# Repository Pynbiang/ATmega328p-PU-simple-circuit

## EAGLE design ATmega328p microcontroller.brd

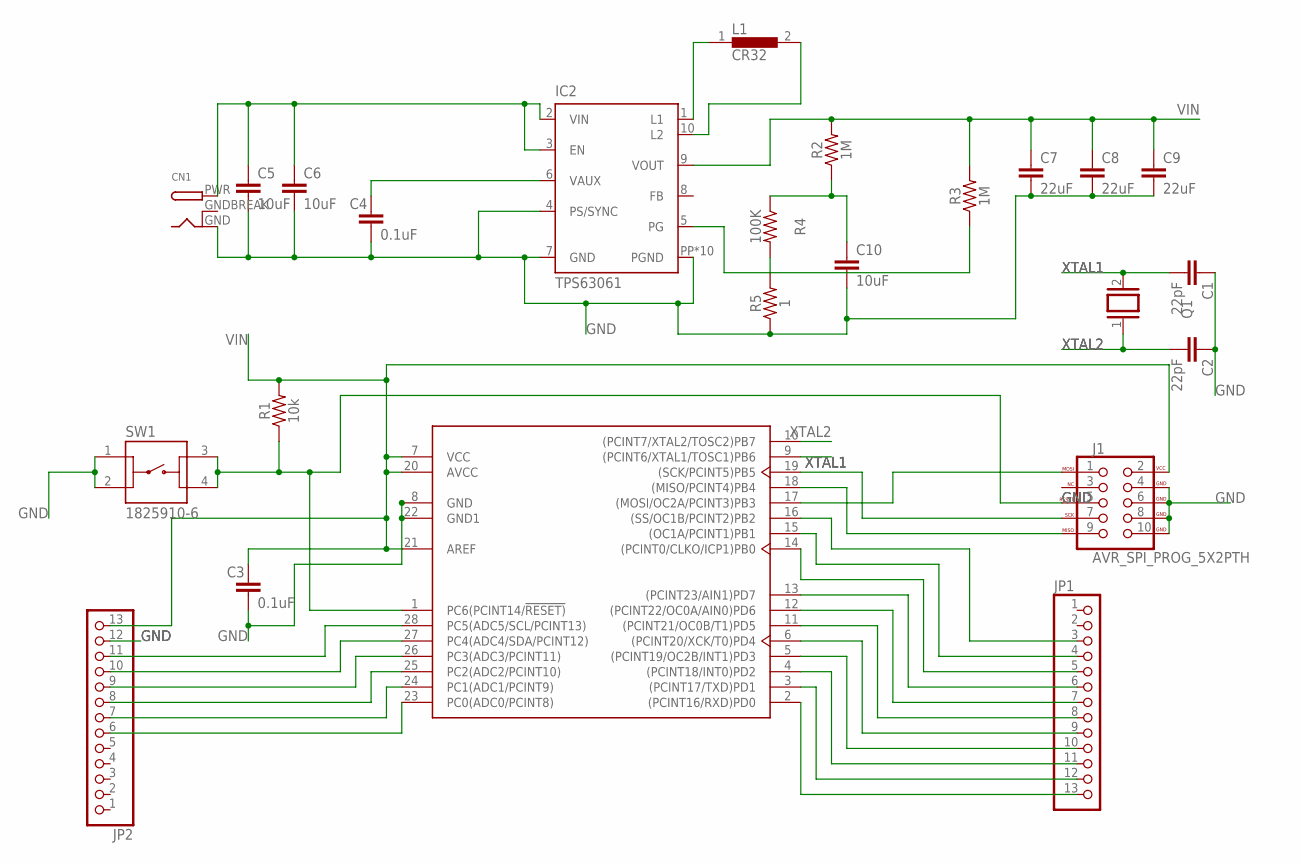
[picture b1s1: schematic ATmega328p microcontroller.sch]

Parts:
C1, C2: 22pF; 0603
C3, C4: 0.1uF; 0402
C5, C6, C10: 10uF; 0603
C7, C8, C9: 22uF; 0805
CN1: DCBARRELPTH; DCJACK_2MM_PTH
IC2: TPS63061; DSC-S-PWSON-N10
J1: AVR_SPI_PROG_5X2PTH; 2X5
JP1, JP2: PINHD-1X13; 1X13
L1: CR32
Q1: XTAL/S; QS
R1: 10k; 0603
R2, R3: 1M; 0603
R4: 100K; 0402
R5: 1; 0603
SW1: 1825910-6
U1: ATMEGA328P-PU; DIP-28

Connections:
GND: C1.1, C2.1, C3.2, C4.2, C5.2, C6.2, C7.2, C8.2, C9.2, C10.2, CN1.GND, IC2.4 (PS/SYNC), IC2.7 (GND), IC2.PP (PGND), IC2.PP@1 (PGND), IC2.PP@2 (PGND), IC2.PP@3 (PGND), IC2.PP@4 (PGND), IC2.PP@5 (PGND), IC2.PP@7 (PGND), IC2.PP@8 (PGND), IC2.PP@9 (PGND), IC2.PP@10 (PGND), J1.4 (GND), J1.6 (GND), J1.8 (GND), J1.10 (GND), JP2.12, R5.1, SW1.1, SW1.2, U1.8 (GND), U1.22 (GND1)
GNDBREAK: CN1.GNDBREAK
unnamed: JP2.11, U1.28 (PC5(ADC5/SCL/PCINT13))
unnamed: J1.7 (SCK), U1.19 ((SCK/PCINT5)PB5)
unnamed: J1.9 (MISO), U1.18 ((MISO/PCINT4)PB4)
unnamed: J1.1 (MOSI), U1.17 ((MOSI/OC2A/PCINT3)PB3)
unnamed: J1.5 (RESET), R1.1, SW1.3, SW1.4, U1.1 (PC6(PCINT14/!RESET))
unnamed: JP1.9, U1.6 ((PCINT20/XCK/T0)PD4)
unnamed: JP1.8, U1.11 ((PCINT21/OC0B/T1)PD5)
unnamed: JP1.7, U1.12 ((PCINT22/OC0A/AIN0)PD6)
unnamed: JP1.13, U1.2 ((PCINT16/RXD)PD0)
unnamed: JP1.12, U1.3 ((PCINT17/TXD)PD1)
unnamed: JP1.11, U1.4 ((PCINT18/INT0)PD2)
unnamed: JP1.10, U1.5 ((PCINT19/OC2B/INT1)PD3)
unnamed: JP1.6, U1.13 ((PCINT23/AIN1)PD7)
unnamed: JP1.5, U1.14 ((PCINT0/CLKO/ICP1)PB0)
unnamed: JP1.4, U1.15 ((OC1A/PCINT1)PB1)
unnamed: JP1.3, U1.16 ((SS/OC1B/PCINT2)PB2)
unnamed: JP2.10, U1.27 (PC4(ADC4/SDA/PCINT12))
unnamed: JP2.9, U1.26 (PC3(ADC3/PCINT11))
unnamed: JP2.8, U1.25 (PC2(ADC2/PCINT10))
unnamed: JP2.7, U1.24 (PC1(ADC1/PCINT9))
unnamed: JP2.6, U1.23 (PC0(ADC0/PCINT8))
unnamed: C5.1, C6.1, CN1.PWR, IC2.2 (VIN), IC2.3 (EN)
unnamed: C4.1, IC2.6 (VAUX)
unnamed: IC2.1 (L1), L1.1
unnamed: IC2.10 (L2), L1.2
unnamed: C10.1, R2.1, R4.1
unnamed: R4.2, R5.2
unnamed: IC2.5 (PG), R3.1
VIN: C3.1, C7.1, C8.1, C9.1, IC2.9 (VOUT), J1.2 (VCC), JP2.13, R1.2, R2.2, R3.2, U1.7 (VCC), U1.20 (AVCC), U1.21 (AREF)
XTAL1: C1.2, Q1.2, U1.9 ((PCINT6/XTAL1/TOSC1)PB6)
XTAL2: C2.2, Q1.1, U1.10 ((PCINT7/XTAL2/TOSC2)PB7)

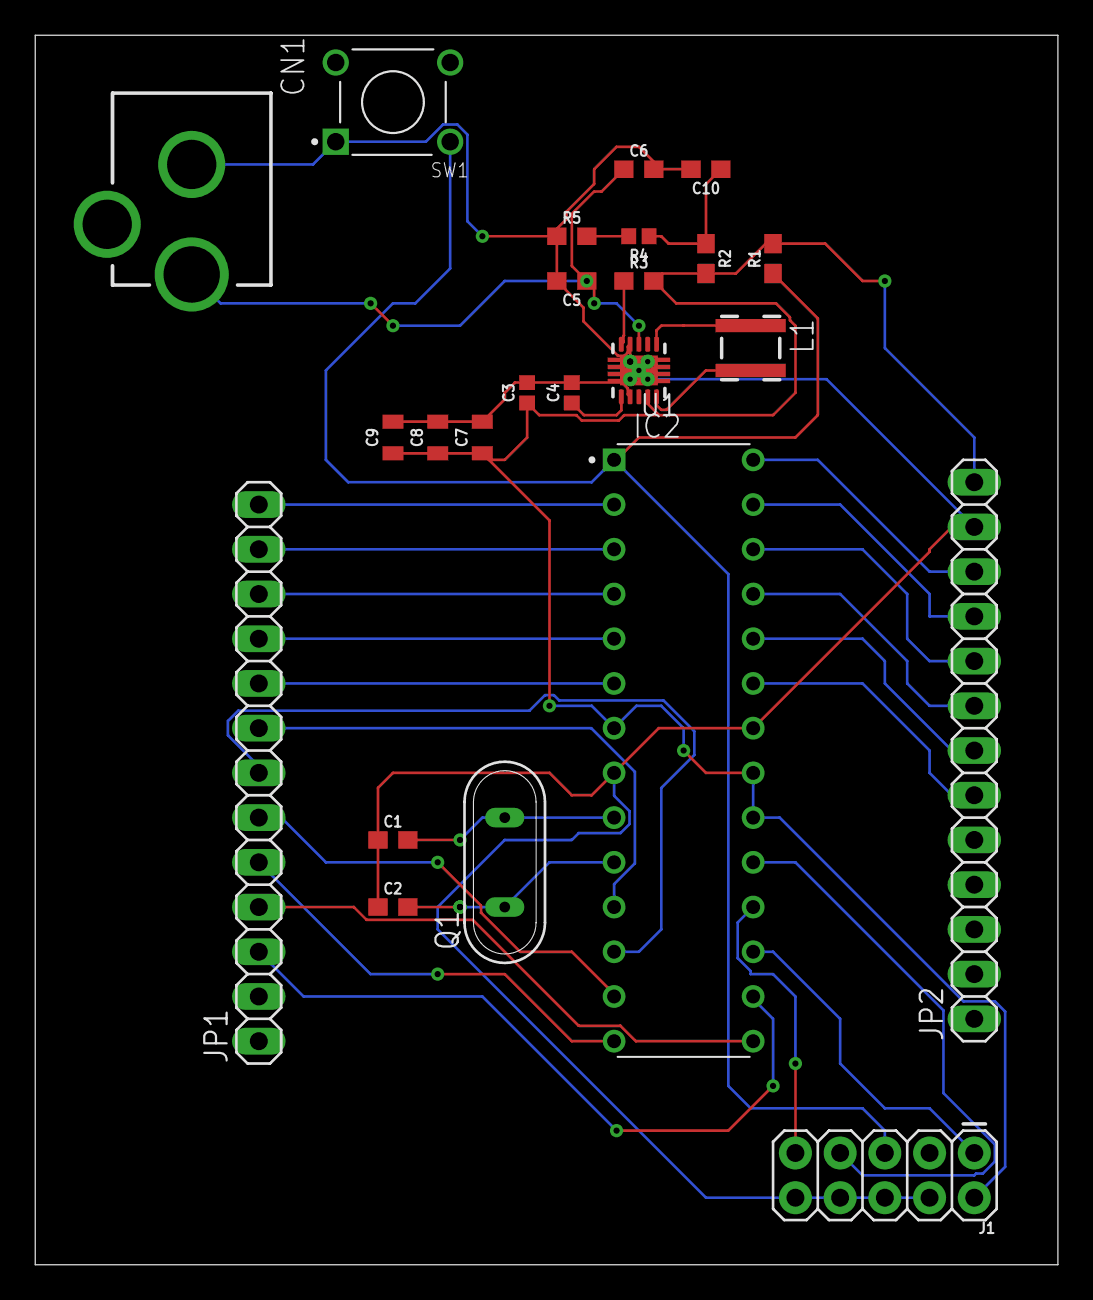
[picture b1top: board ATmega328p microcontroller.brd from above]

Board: 2 copper layers, 58.1 x 69.8 mm, 24 parts (0 on the bottom side), 32 nets.

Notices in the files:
parts and their libraries:
SparkFun-Capacitors: Licensing: Creative Commons ShareAlike 4.0 International - https://creativecommons.org/licenses/by-sa/4.0
